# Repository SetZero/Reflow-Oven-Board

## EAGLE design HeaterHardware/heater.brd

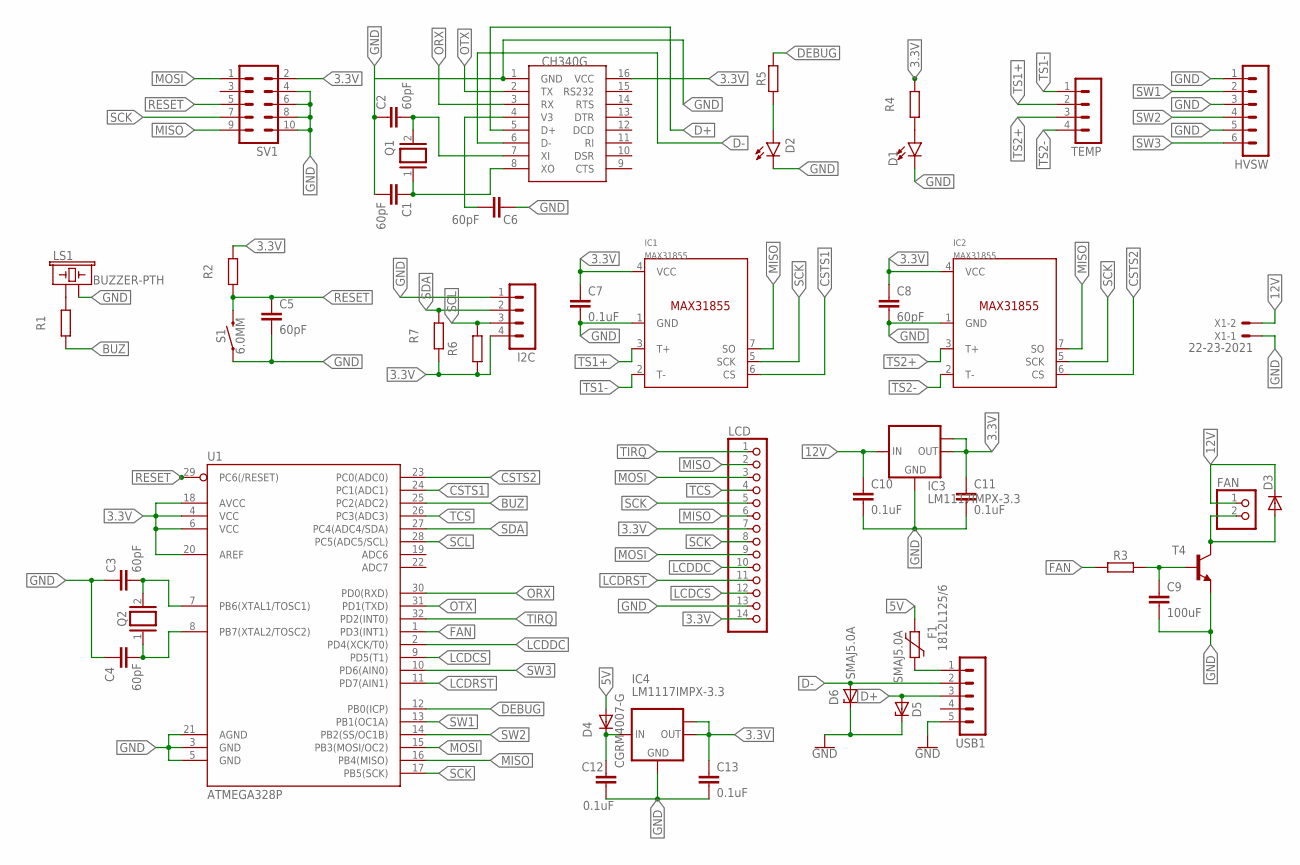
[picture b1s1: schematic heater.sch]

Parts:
C1, C2, C3, C4, C5, C6, C8: 60pF; C0805
C7, C10, C11, C12, C13: 0.1uF; C0805
C9: 100uF; C0805
D1, D2: LED5MM; LED_5MM
D3, D4: CGRM4007-G; SOD-123_MINI-SMA
D5, D6: SMAJ5.0A; DO214AC
F1: 1812L125/6; 1812L
FAN: PINHD-1X2; 1X02
HVSW: MA06-1
I2C: MA04-1
IC1, IC2: MAX31855; SOIC8
IC3, IC4: LM1117IMPX-3.3; SOT223
LCD: PINHD-1X14; 1X14
LS1: BUZZER-PTH; BUZZER-12MM
Q1, Q2: XTAL/S; QS
R1, R2, R3, R4, R5, R6, R7: M0805
S1: 6.0MM; TACTILE_SWITCH_PTH_6.0MM
SV1: MA05-2
T4: TRANSISTOR_2SC2509V; TRANSISTOR_TO220AV
TEMP: MA04-1
U1: ATMEGA328P; TQFP32-08
U$1: CH340G; SOIC16
USB1: MA05-1
X1: 22-23-2021

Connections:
3.3V: C7.1, C8.1, C11.1, C13.1, I2C.4, IC1.4 (VCC), IC2.4 (VCC), IC3.2 (OUT), IC3.TAB (OUT1), IC4.2 (OUT), IC4.TAB (OUT1), LCD.7, LCD.14, R2.2, R4.2, R6.1, R7.1, SV1.2, U1.4 (VCC), U1.6 (VCC), U1.18 (AVCC), U1.20 (AREF), U$1.16 (VCC)
5V: D4.A, F1.2
12V: C10.1, D3.C, FAN.1, IC3.3 (IN), X1.2
BUZ: R1.1, U1.25 (PC2(ADC2))
CSTS1: IC1.6 (CS), U1.24 (PC1(ADC1))
CSTS2: IC2.6 (CS), U1.23 (PC0(ADC0))
D+: D5.A, U$1.5 (D+), USB1.3
D-: D6.A, U$1.6 (D-), USB1.2
DEBUG: R5.2, U1.12 (PB0(ICP))
FAN: R3.1, U1.1 (PD3(INT1))
FAN_PRE: D3.A, FAN.2, T4.2 (C)
GND: C1.2, C2.1, C3.1, C4.1, C5.2, C6.1, C7.2, C8.2, C9.2, C10.2, C11.2, C12.2, C13.2, D1.K (C), D2.K (C), D5.C, D6.C, HVSW.1, HVSW.3, HVSW.5, I2C.1, IC1.1 (GND), IC2.1 (GND), IC3.1 (GND), IC4.1 (GND), LCD.13, LS1.- (2), S1.1, SV1.4, SV1.6, SV1.8, SV1.10, T4.3 (E), U1.3 (GND), U1.5 (GND), U1.21 (AGND), U$1.1 (GND), USB1.5, X1.1
LCDCS: LCD.12, U1.9 (PD5(T1))
LCDDC: LCD.10, U1.2 (PD4(XCK/T0))
LCDRST: LCD.11, U1.11 (PD7(AIN1))
MISO: IC1.7 (SO), IC2.7 (SO), LCD.2, LCD.6, SV1.9, U1.16 (PB4(MISO))
MOSI: LCD.3, LCD.9, SV1.1, U1.15 (PB3(MOSI/OC2))
unnamed: C1.1, Q1.1, U$1.8 (XO)
unnamed: C2.2, Q1.2, U$1.7 (XI)
unnamed: C12.1, D4.C, IC4.3 (IN)
unnamed: LS1.+ (1), R1.2
unnamed: C6.2, U$1.4 (V3)
unnamed: C9.1, R3.2, T4.1 (B)
unnamed: D1.A, R4.1
unnamed: D2.A, R5.1
ORX: U1.30 (PD0(RXD)), U$1.3 (RX)
OTX: U1.31 (PD1(TXD)), U$1.2 (TX)
PRE5V: F1.1, USB1.1
RESET: C5.1, R2.1, S1.3 (2), SV1.5, U1.29 (PC6(/RESET))
SCK: IC1.5 (SCK), IC2.5 (SCK), LCD.5, LCD.8, SV1.7, U1.17 (PB5(SCK))
SCL: I2C.3, R6.2, U1.28 (PC5(ADC5/SCL))
SDA: I2C.2, R7.2, U1.27 (PC4(ADC4/SDA))
SW1: HVSW.2, U1.13 (PB1(OC1A))
SW2: HVSW.4, U1.14 (PB2(SS/OC1B))
SW3: HVSW.6, U1.10 (PD6(AIN0))
TCS: LCD.4, U1.26 (PC3(ADC3))
TIRQ: LCD.1, U1.32 (PD2(INT0))
TS1+: IC1.3 (T+), TEMP.2
TS1-: IC1.2 (T-), TEMP.1
TS2+: IC2.3 (T+), TEMP.3
TS2-: IC2.2 (T-), TEMP.4
XTAL1: C4.2, Q2.1, U1.8 (PB7(XTAL2/TOSC2))
XTAL2: C3.2, Q2.2, U1.7 (PB6(XTAL1/TOSC1))

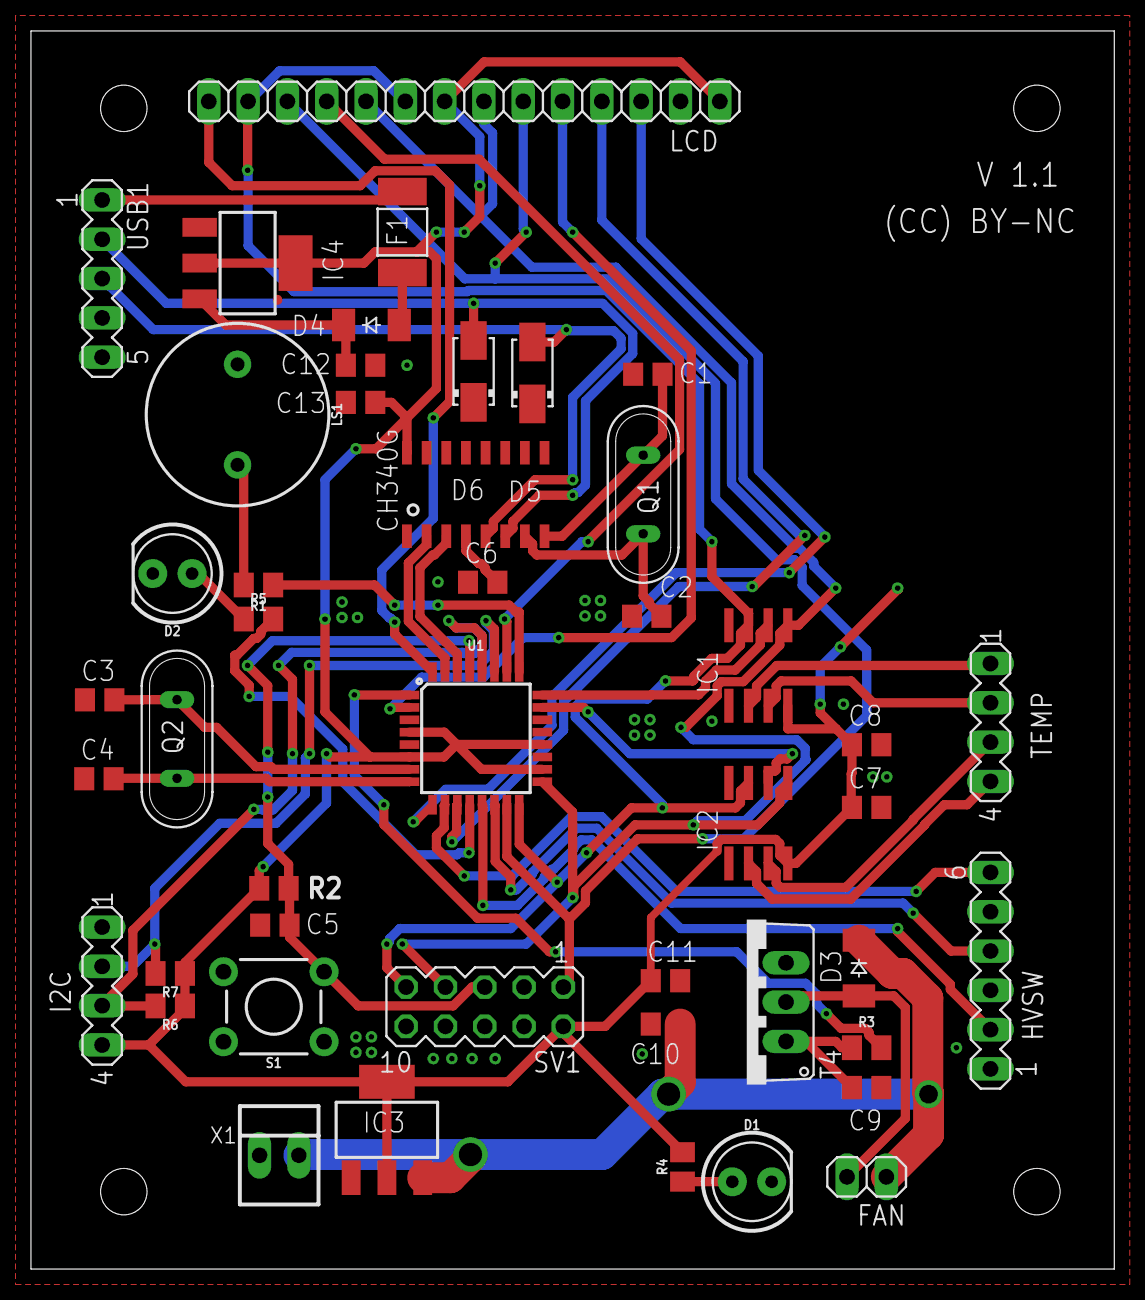
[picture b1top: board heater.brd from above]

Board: 2 copper layers, 70.0 x 80.0 mm, 46 parts (0 on the bottom side), 43 nets.

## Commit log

2018-12-16 Initial file commit
2018-12-16 new gitignore
2018-12-16 gitignore update
2018-12-16 improved routing

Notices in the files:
parts and their libraries:
SparkFun-LED: Licensing: Creative Commons ShareAlike 4.0 International - https://creativecommons.org/licenses/by-sa/4.0
